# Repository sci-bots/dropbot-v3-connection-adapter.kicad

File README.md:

# DropBot v3 connection adapter board

This adapter allows you to breakout the signals from a DropBot v3's pogo pins. It can be used to connect to an externally mounted DMF chip using [Samtec SFSD cables](https://www.samtec.com/products/sfsd) (e.g., 1 x `SFSD-25-28-G-24.00-D-NDX` and 2 x `SFSD-20-28-G-24.00-D-NDX`).

.

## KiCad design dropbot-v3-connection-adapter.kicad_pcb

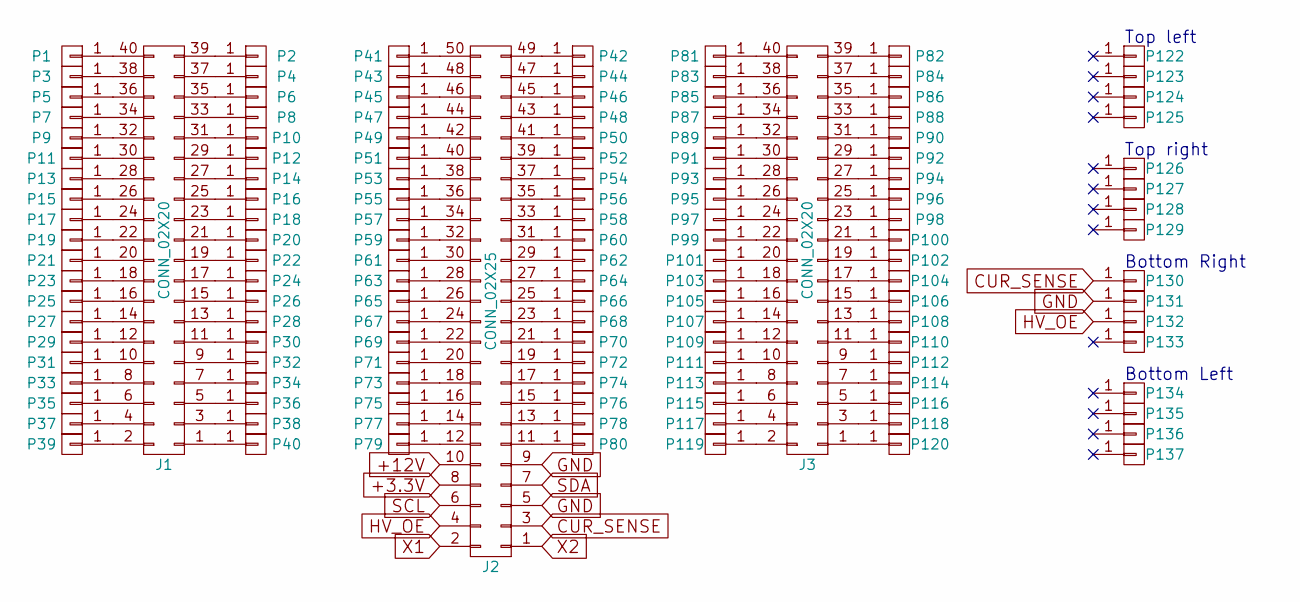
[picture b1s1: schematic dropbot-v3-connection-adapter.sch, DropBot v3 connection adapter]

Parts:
J1, J3: CONN_02X20; TFML-120-02-S-D; Mfg_Part_No TFML-120-02-S-D
J2: CONN_02X25; TFML-125-02-S-D; Mfg_Part_No TFML-125-02-S-D
P1, P2, P3, P4, P5, P6, P7, P8, P9, P10, P11, P12, P13, P14, P15, P16, P17, P18, P19, P20, P21, P22, P23, P24, P25, P26, P27, P28, P29, P30, P31, P32, P33, P34, P35, P36, P37, P38, P39, P40, P41, P42, P43, P44, P45, P46, P47, P48, P49, P50, P51, P52, P53, P54, P55, P56, P57, P58, P59, P60, P61, P62, P63, P64, P65, P66, P67, P68, P69, P70, P71, P72, P73, P74, P75, P76, P77, P78, P79, P80, P81, P82, P83, P84, P85, P86, P87, P88, P89, P90, P91, P92, P93, P94, P95, P96, P97, P98, P99, P100, P101, P102, P103, P104, P105, P106, P107, P108, P109, P110, P111, P112, P113, P114, P115, P116, P117, P118, P119, P120, P122, P123, P124, P125, P126, P127, P128, P129, P130, P131, P132, P133, P134, P135, P136, P137: CONN_01X01; 1.9mm_DMF_Electrode

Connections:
+3.3V: J2.8
+12V: J2.10
CUR_SENSE: J2.3, P130.1
GND: J2.5, J2.9, P131.1
HV_OE: J2.4, P132.1
unnamed: J1.1, P40.1
unnamed: J1.2, P39.1
unnamed: J1.3, P38.1
unnamed: J1.4, P37.1
unnamed: J1.5, P36.1
unnamed: J1.6, P35.1
unnamed: J1.7, P34.1
unnamed: J1.8, P33.1
unnamed: J1.9, P32.1
unnamed: J1.10, P31.1
unnamed: J1.11, P30.1
unnamed: J1.12, P29.1
unnamed: J1.13, P28.1
unnamed: J1.14, P27.1
unnamed: J1.15, P26.1
unnamed: J1.16, P25.1
unnamed: J1.17, P24.1
unnamed: J1.18, P23.1
unnamed: J1.19, P22.1
unnamed: J1.20, P21.1
unnamed: J1.21, P20.1
unnamed: J1.22, P19.1
unnamed: J1.23, P18.1
unnamed: J1.24, P17.1
unnamed: J1.25, P16.1
unnamed: J1.26, P15.1
unnamed: J1.27, P14.1
unnamed: J1.28, P13.1
unnamed: J1.29, P12.1
unnamed: J1.30, P11.1
unnamed: J1.31, P10.1
unnamed: J1.32, P9.1
unnamed: J1.33, P8.1
unnamed: J1.34, P7.1
unnamed: J1.35, P6.1
unnamed: J1.36, P5.1
unnamed: J1.37, P4.1
unnamed: J1.38, P3.1
unnamed: J1.39, P2.1
unnamed: J1.40, P1.1
unnamed: J2.11, P80.1
unnamed: J2.12, P79.1
unnamed: J2.13, P78.1
unnamed: J2.14, P77.1
unnamed: J2.15, P76.1
unnamed: J2.16, P75.1
unnamed: J2.17, P74.1
unnamed: J2.18, P73.1
unnamed: J2.19, P72.1
unnamed: J2.20, P71.1
unnamed: J2.21, P70.1
unnamed: J2.22, P69.1
unnamed: J2.23, P68.1
unnamed: J2.24, P67.1
unnamed: J2.25, P66.1
unnamed: J2.26, P65.1
unnamed: J2.27, P64.1
unnamed: J2.28, P63.1
unnamed: J2.29, P62.1
unnamed: J2.30, P61.1
unnamed: J2.31, P60.1
unnamed: J2.32, P59.1
unnamed: J2.33, P58.1
unnamed: J2.34, P57.1
unnamed: J2.35, P56.1
unnamed: J2.36, P55.1
unnamed: J2.37, P54.1
unnamed: J2.38, P53.1
unnamed: J2.39, P52.1
unnamed: J2.40, P51.1
unnamed: J2.41, P50.1
unnamed: J2.42, P49.1
unnamed: J2.43, P48.1
unnamed: J2.44, P47.1
unnamed: J2.45, P46.1
unnamed: J2.46, P45.1
unnamed: J2.47, P44.1
unnamed: J2.48, P43.1
unnamed: J2.49, P42.1
unnamed: J2.50, P41.1
unnamed: J3.1, P120.1
unnamed: J3.2, P119.1
unnamed: J3.3, P118.1
unnamed: J3.4, P117.1
unnamed: J3.5, P116.1
unnamed: J3.6, P115.1
unnamed: J3.7, P114.1
unnamed: J3.8, P113.1
unnamed: J3.9, P112.1
unnamed: J3.10, P111.1
unnamed: J3.11, P110.1
unnamed: J3.12, P109.1
unnamed: J3.13, P108.1
unnamed: J3.14, P107.1
unnamed: J3.15, P106.1
unnamed: J3.16, P105.1
unnamed: J3.17, P104.1
unnamed: J3.18, P103.1
unnamed: J3.19, P102.1
unnamed: J3.20, P101.1
unnamed: J3.21, P100.1
unnamed: J3.22, P99.1
unnamed: J3.23, P98.1
unnamed: J3.24, P97.1
unnamed: J3.25, P96.1
unnamed: J3.26, P95.1
unnamed: J3.27, P94.1
unnamed: J3.28, P93.1
unnamed: J3.29, P92.1
unnamed: J3.30, P91.1
unnamed: J3.31, P90.1
unnamed: J3.32, P89.1
unnamed: J3.33, P88.1
unnamed: J3.34, P87.1
unnamed: J3.35, P86.1
unnamed: J3.36, P85.1
unnamed: J3.37, P84.1
unnamed: J3.38, P83.1
unnamed: J3.39, P82.1
unnamed: J3.40, P81.1
SCL: J2.6
SDA: J2.7
X1: J2.2
X2: J2.1

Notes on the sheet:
Top left
Top right
Bottom Left
Bottom Right

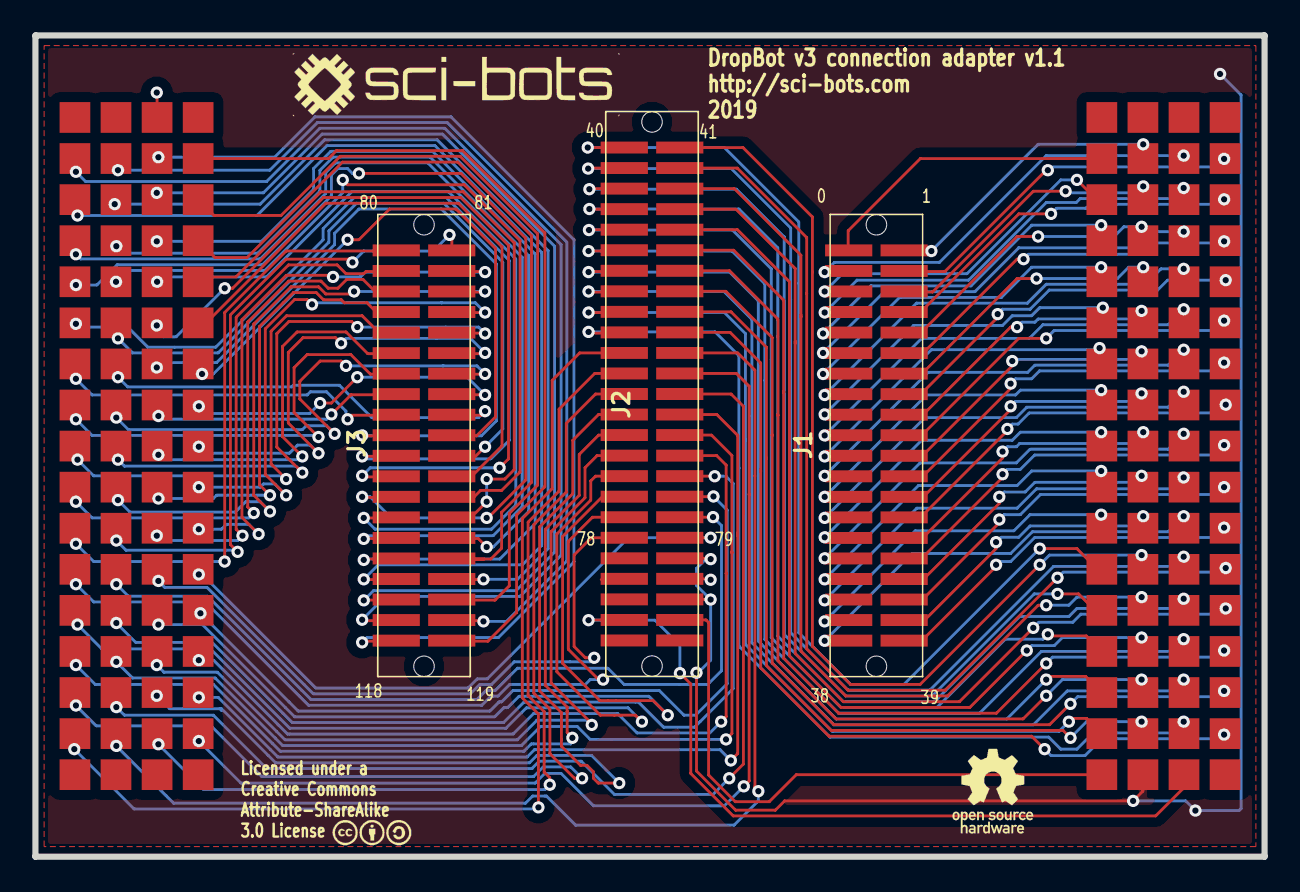
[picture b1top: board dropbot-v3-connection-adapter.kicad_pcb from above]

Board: 2 copper layers, 76.0 x 50.8 mm, 139 parts (0 on the bottom side), 123 nets.

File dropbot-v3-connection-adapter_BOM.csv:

Reference,Value,Footprint,Count,Datasheet,Mfg_Part_No
"P1, P2, P3, P4, P5, P6, P7, P8, P9, P10, P11, P12, P13, P14, P15, P16, P17, P18, P19, P20, P21, P22, P23, P24, P25, P26, P27, P28, P29, P30, P31, P32, P33, P34, P35, P36, P37, P38, P39, P40, P41, P42, P43, P44, P45, P46, P47, P48, P49, P50, P51, P52, P53, P54, P55, P56, P57, P58, P59, P60, P61, P62, P63, P64, P65, P66, P67, P68, P69, P70, P71, P72, P73, P74, P75, P76, P77, P78, P79, P80, P81, P82, P83, P84, P85, P86, P87, P88, P89, P90, P91, P92, P93, P94, P95, P96, P97, P98, P99, P100, P101, P102, P103, P104, P105, P106, P107, P108, P109, P110, P111, P112, P113, P114, P115, P116, P117, P118, P119, P120, P122, P125, P126, P127, P128, P129, P124, P123, P137, P136, P135, P134, P133, P132, P131, P130",CONN_01X01,wheelerlab:1.9mm_DMF_Electrode,136,,
"J1, J3",CONN_02X20,WheelerLab:TFML-120-02-S-D,2,,TFML-120-02-S-D
J2,CONN_02X25,WheelerLab:TFML-125-02-S-D,1,,TFML-125-02-S-D

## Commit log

2017-04-12 Create based on 120-channel-test-board
2017-08-08 Add README.md
2019-06-13 New adapter board that breaks out all pins
    * 2 connectors with 40 pins and 1 connector with 50 pins
    * extra 10 pins include HVOE, GND and current sensing
2021-06-10 Fix connector orientation

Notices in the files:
dropbot-v3-connection-adapter.kicad_pcb:
Licensed under a
Creative Commons
Attribute-ShareAlike
